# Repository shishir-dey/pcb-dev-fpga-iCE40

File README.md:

# pcb-dev-fpga-iCE40

Reference: [iCEBreaker FPGA](https://github.com/icebreaker-fpga/icebreaker)

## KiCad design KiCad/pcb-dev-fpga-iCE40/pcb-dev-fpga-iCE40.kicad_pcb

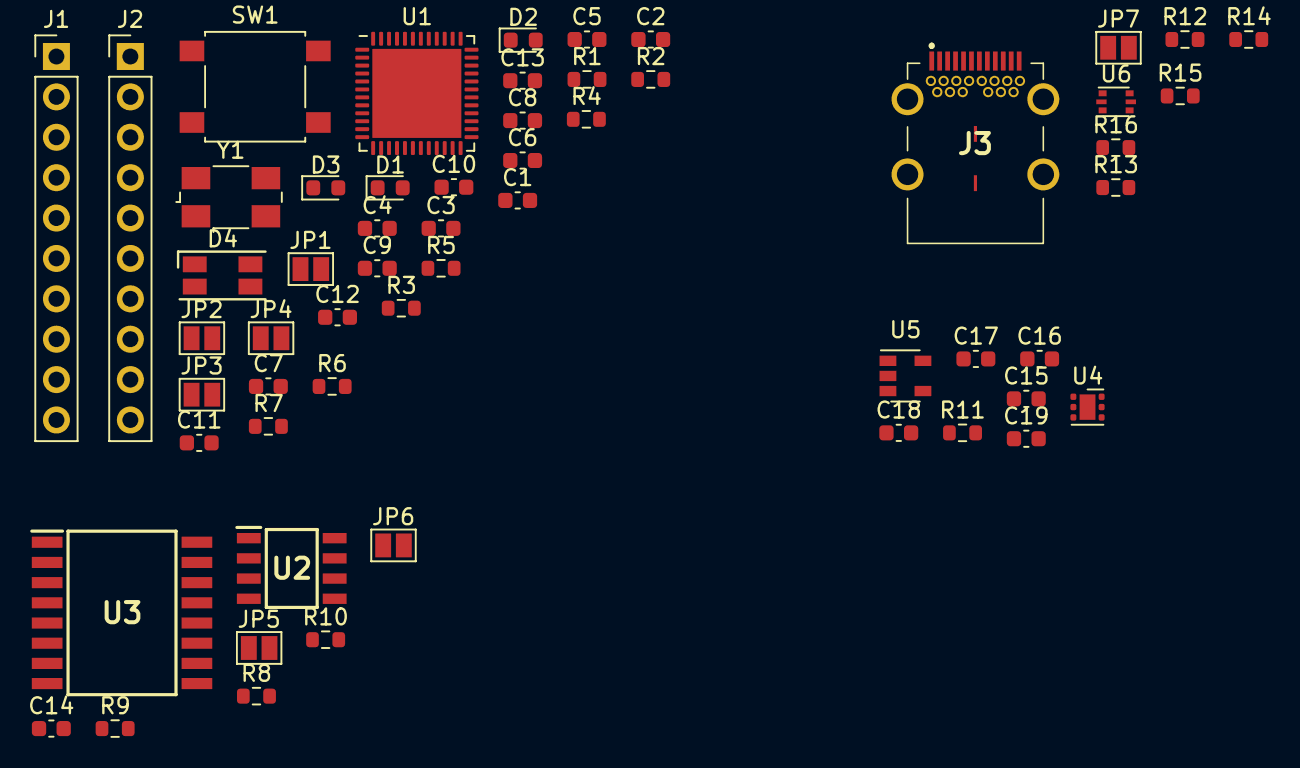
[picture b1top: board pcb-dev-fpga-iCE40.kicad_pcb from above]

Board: 2 copper layers, 57 parts (0 on the bottom side), 53 nets, no tracks yet.

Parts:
C1, C2, C3, C4, C6, C7, C11, C12, C14: 100n; C_0603_1608Metric
C5, C9, C15: 1u; C_0603_1608Metric
C8, C13: 10n; C_0603_1608Metric
C10: 10u; C_0603_1608Metric
C16, C17, C18, C19: 4u7; C_0603_1608Metric
D1: RED_LED; LED_0603_1608Metric
D2: GREEN_LED; LED_0603_1608Metric
D3: BLUE_LED; LED_0603_1608Metric
D4: RGB LED; LED_RGB_1210
J1: Header 1; PinHeader_1x10_P2.54mm_Vertical
J2: Header 2; PinHeader_1x10_P2.54mm_Vertical
J3: USB-C Receptacle (USB2.0); 632723300021
JP1, JP2, JP3, JP4, JP5, JP6, JP7: Jumper; SolderJumper-2_P1.3mm_Open_Pad1.0x1.5mm
R1, R2, R3: 2k2; R_0603_1608Metric
R4, R5, R6, R8, R9, R10, R11: 10k; R_0603_1608Metric
R7: 100e; R_0603_1608Metric
R12, R13: 5k1; R_0603_1608Metric
R14: 1k5; R_0603_1608Metric
R15, R16: 22e; R_0603_1608Metric
SW1: SPST Switch; SW_SPST_B3S-1000
U1: ICE40UP5K-SG48ITR; QFN-48-1EP_7x7mm_P0.5mm_EP5.6x5.6mm
U2: LY68L6400; SOIC127P600X175-8N
U3: W25Q128JVxxM; SOIC127P1032X264-16N
U4: TLV75533PDRV; WSON-6-1EP_2x2mm_P0.65mm_EP1x1.6mm
U5: TLV73312PDBV; SOT-23-5
U6: USBLC6-2P6; SOT-666
Y1: 12MHz; Crystal_SMD_0603-4Pin_6.0x3.5mm

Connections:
+1V2: C5.1, C7.1, C8.1, C9.1, C11.1, C13.1, C19.1, R7.1, U1.5, U1.30, U5.5
+3V3: C2.1, C14.1, C17.1, D4.4, J1.4, JP1.1, JP2.1, JP3.1, JP4.2, R1.1, R2.1, R3.1, R4.1, R5.1, R8.1, R9.1, R10.1, U2.8, U3.8, U4.1, Y1.4
CDONE: D3.2, R3.2, U1.7
CLK: U1.35, Y1.3
CLK_EN: R5.2, Y1.1
FLASH_~CS: JP6.1, R9.2, U3.1
GND: C1.2, C2.2, C3.2, C4.2, C5.2, C6.2, C7.2, C8.2, C9.2, C10.2, C11.2, C12.2, C13.2, C14.2, C15.2, C16.2, C17.2, C18.2, C19.2, D3.1, J1.5, J3.A1, J3.A12, J3.B1, J3.B12, R12.1, R13.1, SW1.1, U1.49, U2.4, U3.4, U4.3, U4.7, U5.2, U6.2, Y1.2
IOB_5b: J2.10, U1.45
IOB_8a: J2.9, U1.4
IOB_9b: J2.8, U1.3
IOB_13b-~LEDG: D2.1, JP5.2, U1.6
IOB_16a: J2.7, U1.9
IOB_18a: J2.6, U1.10
IOB_20a: J2.5, U1.11
IOB_22b: J2.4, U1.12
IOB_23b: J2.3, U1.21
IOB_24a: J2.2, U1.13
IOB_25b_G3: J2.1, U1.20
IOT_36b-~LEDR: D1.1, U1.25
IOT_37a: J1.8, U1.23
IOT_38b: J1.9, U1.27
IOT_39a: J1.10, U1.26
unnamed: C1.1, JP1.2, U1.33
unnamed: C3.1, JP2.2, U1.22
unnamed: C4.1, JP3.2, U1.1
unnamed: C6.1, JP4.1, U1.24
unnamed: C10.1, C12.1, R7.2, U1.29
unnamed: C15.1, R11.1, U4.4
unnamed: D1.2, R1.2
unnamed: D2.2, R2.2
unnamed: J3.A5, R12.2
unnamed: J3.A6, J3.B6, U6.3
unnamed: J3.A7, J3.B7, U6.1
unnamed: J3.B5, R13.2
unnamed: R14.2, R16.2, U6.4
unnamed: R15.2, U6.6
RAM_~CS: JP5.1, R8.2, U2.1
SPI_MISO_IO1: U1.17, U2.2, U3.2
SPI_MOSI-IO0: U1.14, U2.5, U3.5
SPI_SCK: R10.2, U1.15, U2.6, U3.6
SPI_~CS: JP6.2, U1.16
SPI_~HLD~-I03: U1.19, U2.7, U3.7
SPI_~WP~-I02: U1.18, U2.3, U3.3
USB_DET: R14.1, U1.37
USB_N: R15.1, U1.38
USB_P: R16.1, U1.42
VBUS: J3.A4, J3.A9, J3.B4, J3.B9, JP7.2, U6.5
VIN: C16.1, C18.1, J1.2, JP7.1, R11.2, U4.6, U5.1, U5.3
~BTN: R6.2, SW1.2, U1.2
~CRESET: R4.2, U1.8
~RGB0: D4.1, U1.39
~RGB1: D4.2, U1.40
~RGB2: D4.3, U1.41

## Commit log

2021-11-19 Add device datasheet
2021-11-19 Create LICENSE
2021-11-19 Add empty KiCad project
2021-11-22 Add library symbols, finish schematics and export PDF
2021-11-26 Assign footprints
2021-11-26 Update PCB from schematics
2021-11-26 Rearrange folder structure
